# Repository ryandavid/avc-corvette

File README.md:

# log4cxx library symbols missing
```
brew edit log4cxx
```

edit the configure step to look like this (add the last two lines):

```
system "./configure", "--disable-debug", "--disable-dependency-tracking",
                          "--prefix=#{prefix}",
                          # Docs won't install on macOS
                          "--disable-doxygen",
                          "--with-apr=/usr/local/Cellar/apr/1.5.2_3/bin/",
                          "--with-apr-util=/usr/local/Cellar/apr-util/1.5.4_4/bin/"
```

brew reinstall --build-from-source log4cxx

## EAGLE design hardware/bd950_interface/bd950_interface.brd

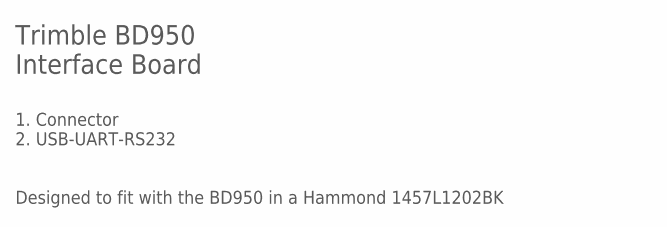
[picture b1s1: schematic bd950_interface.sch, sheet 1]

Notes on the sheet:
Trimble BD950 Interface Board
1. Connector 2. USB-UART-RS232
Designed to fit with the BD950 in a Hammond 1457L1202BK

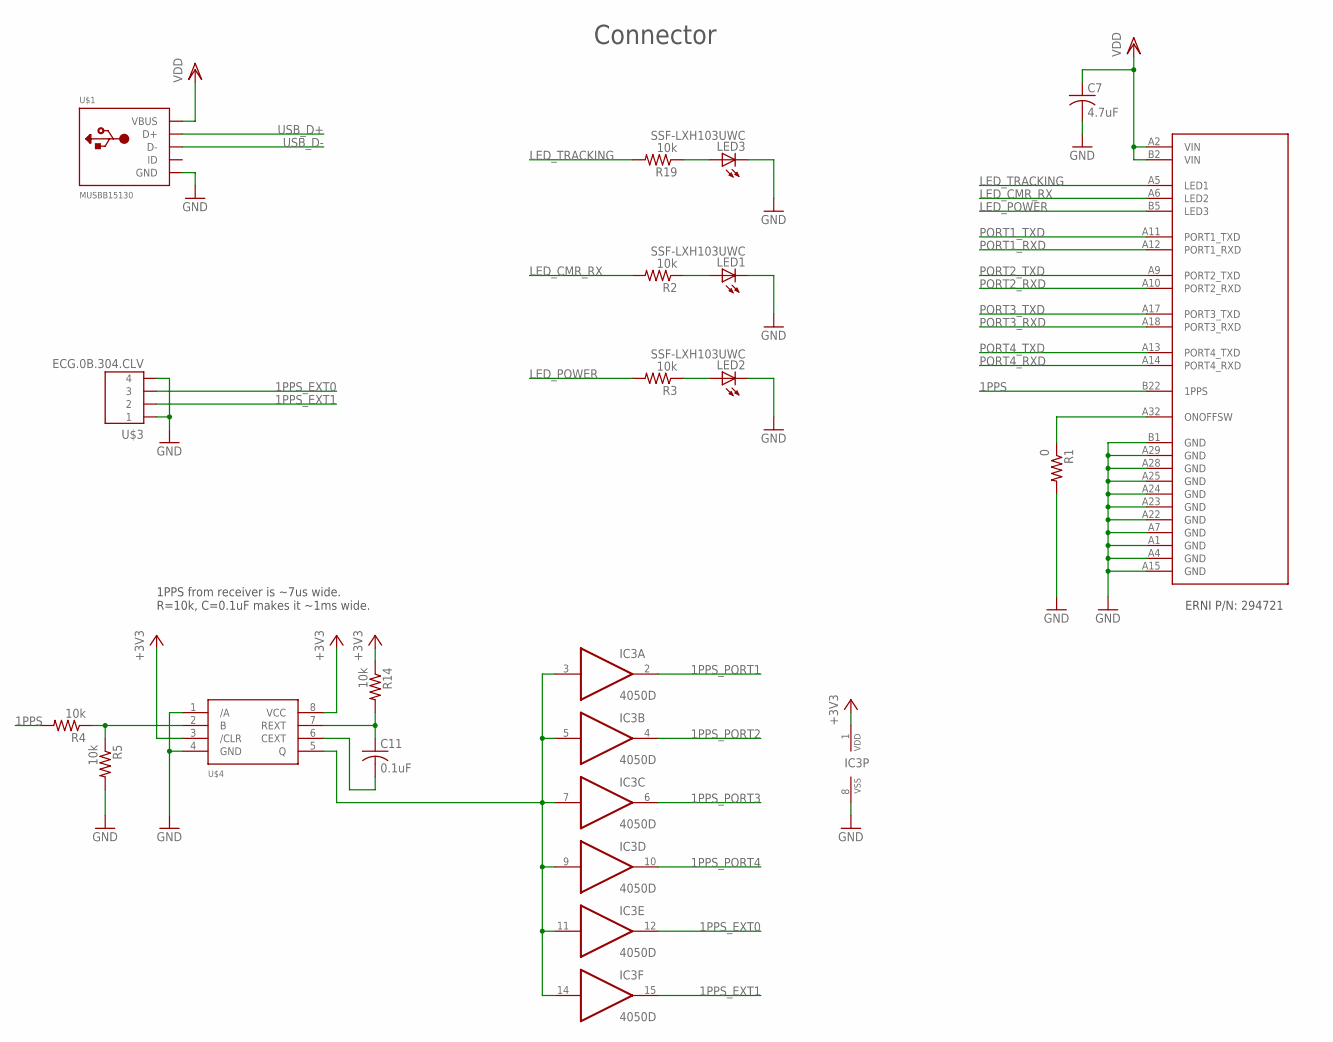
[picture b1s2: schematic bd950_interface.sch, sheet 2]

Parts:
C7: 4.7uF; C0805
C11: 0.1uF; C0603
IC3: 4050D; SO16
LED1, LED2, LED3: SSF-LXH103UWC; CHIP-LED0603
R1: 0; R0603
R2, R3, R4, R5, R14, R19: 10k; R0603
U$1: MUSBB15130
U$2: 294721; TRIMBLE_BD950
U$3: ECG.0B.304.CLV; ECG.0B.CLV
U$4: SN74LVC1G123; DCU_(R-PDSO-G8)

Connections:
1PPS: R4.2, U$2.B22 (1PPS)
1PPS_EXT0: IC3.12 (O), U$3.P$4 (3)
1PPS_EXT1: IC3.15 (O), U$3.P$3 (2)
1PPS_PORT1: IC3.2 (O); also elsewhere on the board
1PPS_PORT2: IC3.4 (O); also elsewhere on the board
1PPS_PORT3: IC3.6 (O); also elsewhere on the board
1PPS_PORT4: IC3.10 (O); also elsewhere on the board
+3V3: IC3.1 (VDD), R14.1, U$4.3 (/CLR), U$4.8 (VCC); also elsewhere on the board
GND: C7.2, IC3.8 (VSS), LED1.C, LED2.C, LED3.C, R1.2, R5.2, U$1.5 (GND), U$2.A1 (GND), U$2.A4 (GND), U$2.A7 (GND), U$2.A15 (GND), U$2.A22 (GND), U$2.A23 (GND), U$2.A24 (GND), U$2.A25 (GND), U$2.A28 (GND), U$2.A29 (GND), U$2.B1 (GND), U$3.P$1 (4), U$3.P$2 (1), U$4.1 (/A), U$4.4 (GND); also elsewhere on the board
LED_CMR_RX: R2.2, U$2.A6 (LED2)
LED_POWER: R3.2, U$2.B5 (LED3)
LED_TRACKING: R19.2, U$2.A5 (LED1)
unnamed: LED1.A, R2.1
unnamed: R1.1, U$2.A32 (ONOFFSW)
unnamed: LED2.A, R3.1
unnamed: LED3.A, R19.1
unnamed: IC3.3 (I), IC3.5 (I), IC3.7 (I), IC3.9 (I), IC3.11 (I), IC3.14 (I), U$4.5 (Q)
unnamed: R4.1, R5.1, U$4.2 (B)
unnamed: C11.2, U$4.6 (CEXT)
unnamed: C11.1, R14.2, U$4.7 (REXT)
PORT1_RXD: U$2.A12 (PORT1_RXD); also elsewhere on the board
PORT1_TXD: U$2.A11 (PORT1_TXD); also elsewhere on the board
PORT2_RXD: U$2.A10 (PORT2_RXD); also elsewhere on the board
PORT2_TXD: U$2.A9 (PORT2_TXD); also elsewhere on the board
PORT3_RXD: U$2.A18 (PORT3_RXD); also elsewhere on the board
PORT3_TXD: U$2.A17 (PORT3_TXD); also elsewhere on the board
PORT4_RXD: U$2.A14 (PORT4_RXD); also elsewhere on the board
PORT4_TXD: U$2.A13 (PORT4_TXD); also elsewhere on the board
USB_D+: U$1.3 (D+); also elsewhere on the board
USB_D-: U$1.2 (D-); also elsewhere on the board
VDD: C7.1, U$1.1 (VBUS), U$2.A2 (VIN), U$2.B2 (VIN); also elsewhere on the board

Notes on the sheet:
Connector
ERNI P/N: 294721
1PPS from receiver is ~7us wide. R=10k, C=0.1uF makes it ~1ms wide.

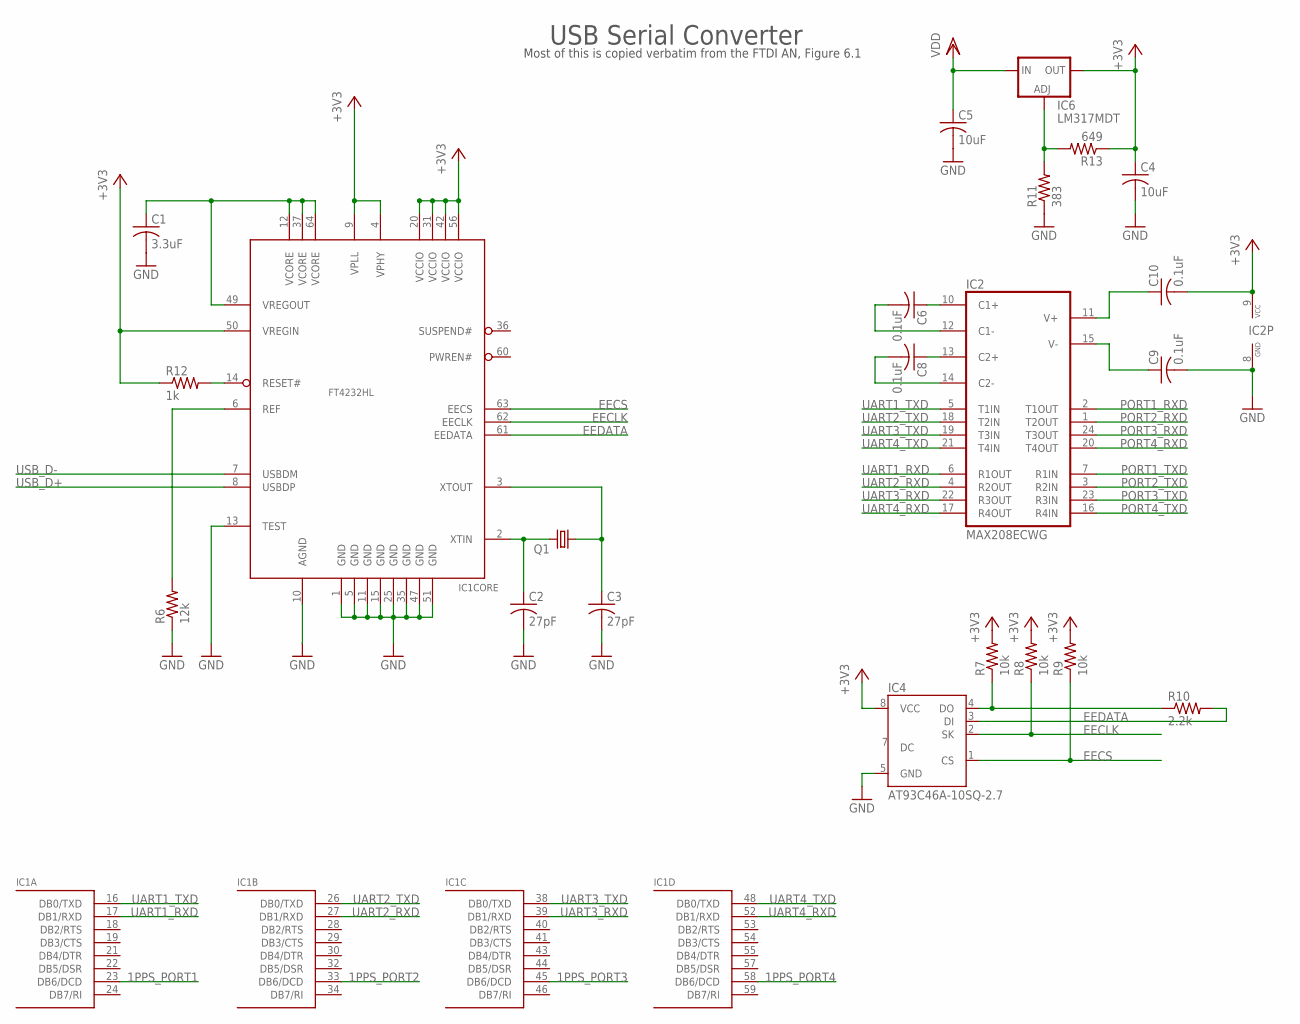
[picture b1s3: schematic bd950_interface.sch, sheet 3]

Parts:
C1: 3.3uF; C0603
C2, C3: 27pF; C0603
C4, C5: 10uF; C0805
C6, C8, C9, C10: 0.1uF; C0603
IC1: FT4232HL; LQFP64
IC2: MAX208ECWG; SO24L
IC4: AT93C46A-10SQ-2.7; SOIC8
IC6: LM317MDT; DPACK
Q1: CRYSTALHC49S; HC49/S
R6: 12k; R0603
R7, R8, R9: 10k; R0603
R10: 2.2k; R0603
R11: 383; R0603
R12: 1k; R0603
R13: 649; R0603

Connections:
1PPS_PORT1: IC1.23 (DB6/DCD); also elsewhere on the board
1PPS_PORT2: IC1.33 (DB6/DCD); also elsewhere on the board
1PPS_PORT3: IC1.45 (DB6/DCD); also elsewhere on the board
1PPS_PORT4: IC1.58 (DB6/DCD); also elsewhere on the board
+3V3: C4.1, C10.2, IC1.4 (VPHY), IC1.9 (VPLL), IC1.20 (VCCIO), IC1.31 (VCCIO), IC1.42 (VCCIO), IC1.50 (VREGIN), IC1.56 (VCCIO), IC2.9 (VCC), IC4.8 (VCC), IC6.4 (OUT), R7.2, R8.2, R9.2, R12.1, R13.1; also elsewhere on the board
EECLK: IC1.62 (EECLK), IC4.2 (SK), R8.1
EECS: IC1.63 (EECS), IC4.1 (CS), R9.1
EEDATA: IC1.61 (EEDATA), IC4.3 (DI), R10.2
GND: C1.2, C2.2, C3.2, C4.2, C5.2, C9.2, IC1.1 (GND), IC1.5 (GND), IC1.10 (AGND), IC1.11 (GND), IC1.13 (TEST), IC1.15 (GND), IC1.25 (GND), IC1.35 (GND), IC1.47 (GND), IC1.51 (GND), IC2.8 (GND), IC4.5 (GND), R6.1, R11.1; also elsewhere on the board
unnamed: IC6.1 (ADJ), R11.2, R13.2
unnamed: IC1.6 (REF), R6.2
unnamed: IC4.4 (DO), R7.1, R10.1
unnamed: C1.1, IC1.12 (VCORE), IC1.37 (VCORE), IC1.49 (VREGOUT), IC1.64 (VCORE)
unnamed: C3.1, IC1.3 (XTOUT), Q1.1
unnamed: C2.1, IC1.2 (XTIN), Q1.2
unnamed: C6.1, IC2.10 (C1+)
unnamed: IC1.14 (RESET#), R12.2
unnamed: C6.2, IC2.12 (C1-)
unnamed: C8.1, IC2.13 (C2+)
unnamed: C8.2, IC2.14 (C2-)
unnamed: C9.1, IC2.15 (V-)
unnamed: C10.1, IC2.11 (V+)
PORT1_RXD: IC2.2 (T1OUT); also elsewhere on the board
PORT1_TXD: IC2.7 (R1IN); also elsewhere on the board
PORT2_RXD: IC2.1 (T2OUT); also elsewhere on the board
PORT2_TXD: IC2.3 (R2IN); also elsewhere on the board
PORT3_RXD: IC2.24 (T3OUT); also elsewhere on the board
PORT3_TXD: IC2.23 (R3IN); also elsewhere on the board
PORT4_RXD: IC2.20 (T4OUT); also elsewhere on the board
PORT4_TXD: IC2.16 (R4IN); also elsewhere on the board
UART1_RXD: IC1.17 (DB1/RXD), IC2.6 (R1OUT)
UART1_TXD: IC1.16 (DB0/TXD), IC2.5 (T1IN)
UART2_RXD: IC1.27 (DB1/RXD), IC2.4 (R2OUT)
UART2_TXD: IC1.26 (DB0/TXD), IC2.18 (T2IN)
UART3_RXD: IC1.39 (DB1/RXD), IC2.22 (R3OUT)
UART3_TXD: IC1.38 (DB0/TXD), IC2.19 (T3IN)
UART4_RXD: IC1.52 (DB1/RXD), IC2.17 (R4OUT)
UART4_TXD: IC1.48 (DB0/TXD), IC2.21 (T4IN)
USB_D+: IC1.8 (USBDP); also elsewhere on the board
USB_D-: IC1.7 (USBDM); also elsewhere on the board
VDD: C5.1, IC6.3 (IN); also elsewhere on the board

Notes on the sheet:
USB Serial Converter
Most of this is copied verbatim from the FTDI AN, Figure 6.1

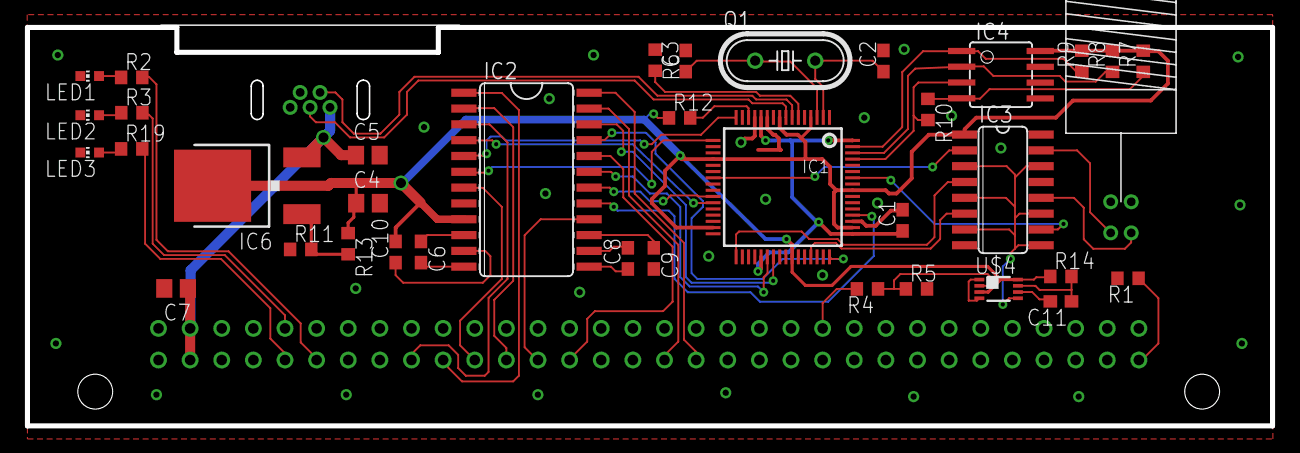
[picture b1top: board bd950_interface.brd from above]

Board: 2 copper layers, 100.0 x 32.0 mm, 39 parts (0 on the bottom side), 55 nets.

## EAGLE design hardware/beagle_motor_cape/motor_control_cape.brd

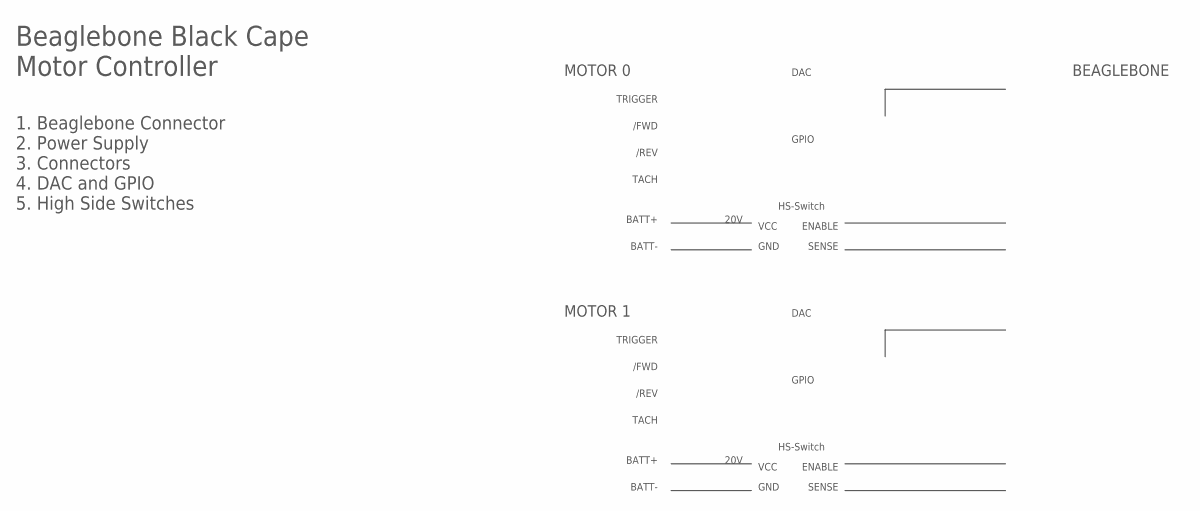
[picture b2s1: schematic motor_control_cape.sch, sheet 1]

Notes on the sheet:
Beaglebone Black Cape Motor Controller
1. Beaglebone Connector 2. Power Supply 3. Connectors 4. DAC and GPIO 5. High Side Switches
MOTOR 0
/FWD
/REV
TACH
BATT+
BATT-
HS-Switch
VCC
GND
ENABLE
SENSE
20V
GPIO
DAC
TRIGGER
MOTOR 1
BEAGLEBONE

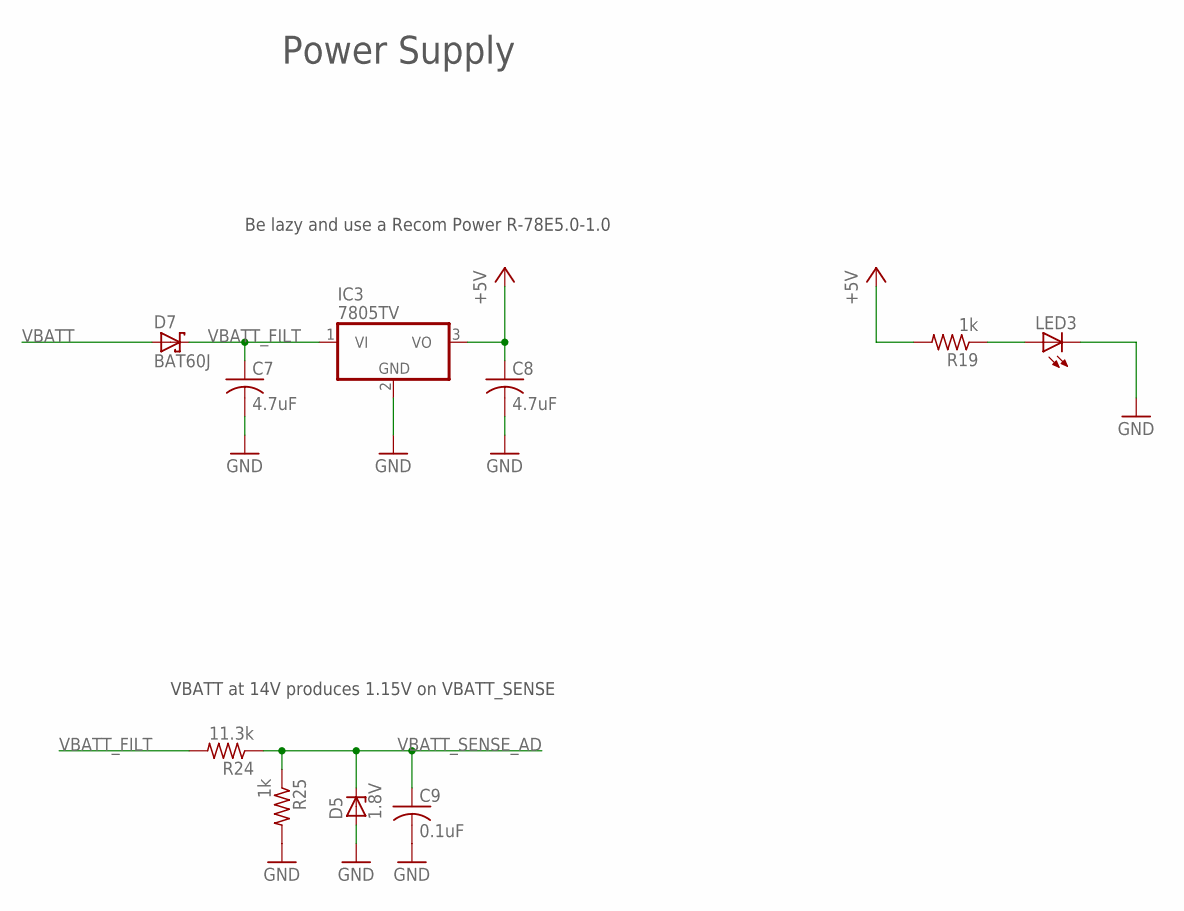
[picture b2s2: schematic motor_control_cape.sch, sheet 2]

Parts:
C7, C8: 4.7uF; C0805
C9: 0.1uF; C0603
D5: 1.8V; SOT23
D7: BAT60J; SOD323_ST
IC3: 7805TV; TO220V
LED3: LEDCHIPLED_0603; CHIPLED_0603
R19, R25: 1k; R0603
R24: 11.3k; R0603

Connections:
+5V: C8.1, IC3.3 (VO), R19.2; also elsewhere on the board
GND: C7.2, C8.2, C9.2, D5.1 (A), IC3.2 (GND), LED3.C, R25.2; also elsewhere on the board
unnamed: LED3.A, R19.1
VBATT: D7.A; also elsewhere on the board
VBATT_FILT: C7.1, D7.C, IC3.1 (VI), R24.2
VBATT_SENSE_AD: C9.1, D5.3 (C), R24.1, R25.1; also elsewhere on the board

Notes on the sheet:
Power Supply
VBATT at 14V produces 1.15V on VBATT_SENSE
Be lazy and use a Recom Power R-78E5.0-1.0

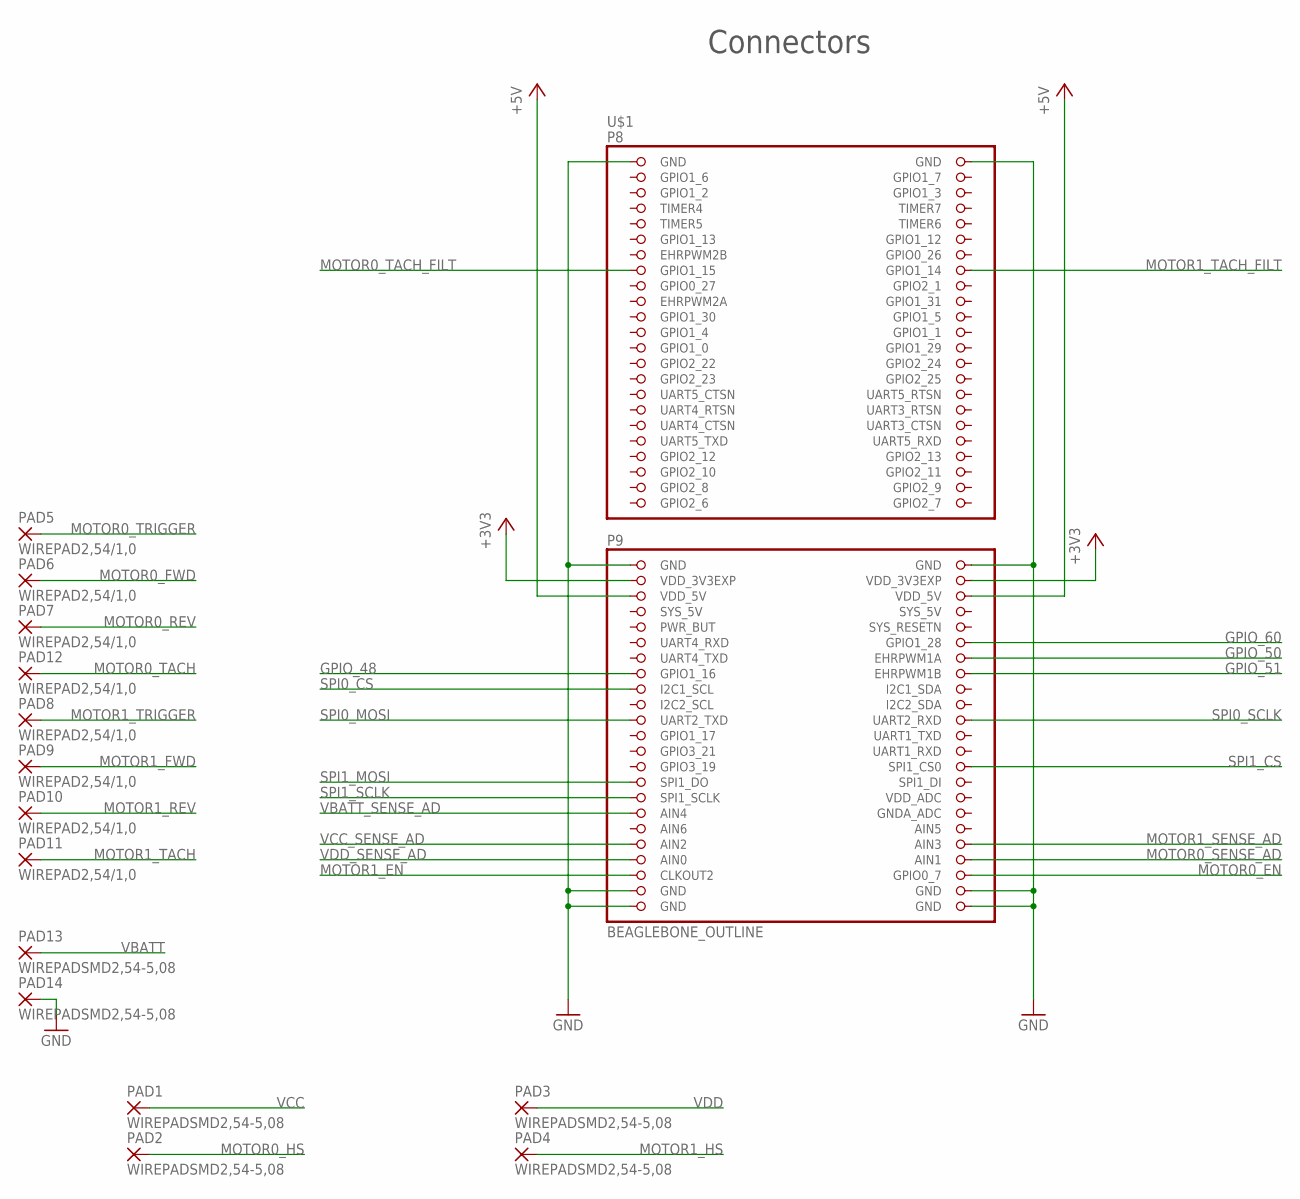
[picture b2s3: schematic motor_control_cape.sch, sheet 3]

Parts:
PAD1, PAD2, PAD3, PAD4, PAD13, PAD14: WIREPADSMD2,54-5,08; SMD2,54-5,08
PAD5, PAD6, PAD7, PAD8, PAD9, PAD10, PAD11, PAD12: WIREPAD2,54/1,0; 2,54/1,0
U$1: BEAGLEBONE_OUTLINE; BEAGLEBONE_SHIELD

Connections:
+3V3: U$1.49 (VDD_3V3EXP), U$1.50 (VDD_3V3EXP); also elsewhere on the board
+5V: U$1.51 (VDD_5V), U$1.52 (VDD_5V); also elsewhere on the board
GND: PAD14.1, U$1.1 (GND), U$1.2 (GND), U$1.47 (GND), U$1.48 (GND), U$1.89 (GND), U$1.90 (GND), U$1.91 (GND), U$1.92 (GND); also elsewhere on the board
GPIO_48: U$1.61 (GPIO1_16); also elsewhere on the board
GPIO_50: U$1.60 (EHRPWM1A); also elsewhere on the board
GPIO_51: U$1.62 (EHRPWM1B); also elsewhere on the board
GPIO_60: U$1.58 (GPIO1_28); also elsewhere on the board
MOTOR0_EN: U$1.88 (GPIO0_7); also elsewhere on the board
MOTOR0_FWD: PAD6.1; also elsewhere on the board
MOTOR0_HS: PAD2.1; also elsewhere on the board
MOTOR0_REV: PAD7.1; also elsewhere on the board
MOTOR0_SENSE_AD: U$1.86 (AIN1); also elsewhere on the board
MOTOR0_TACH: PAD12.1; also elsewhere on the board
MOTOR0_TACH_FILT: U$1.15 (GPIO1_15); also elsewhere on the board
MOTOR0_TRIGGER: PAD5.1; also elsewhere on the board
MOTOR1_EN: U$1.87 (CLKOUT2); also elsewhere on the board
MOTOR1_FWD: PAD9.1; also elsewhere on the board
MOTOR1_HS: PAD4.1; also elsewhere on the board
MOTOR1_REV: PAD10.1; also elsewhere on the board
MOTOR1_SENSE_AD: U$1.84 (AIN3); also elsewhere on the board
MOTOR1_TACH: PAD11.1; also elsewhere on the board
MOTOR1_TACH_FILT: U$1.16 (GPIO1_14); also elsewhere on the board
MOTOR1_TRIGGER: PAD8.1; also elsewhere on the board
SPI0_CS: U$1.63 (I2C1_SCL); also elsewhere on the board
SPI0_MOSI: U$1.67 (UART2_TXD); also elsewhere on the board
SPI0_SCLK: U$1.68 (UART2_RXD); also elsewhere on the board
SPI1_CS: U$1.74 (SPI1_CS0); also elsewhere on the board
SPI1_MOSI: U$1.75 (SPI1_DO); also elsewhere on the board
SPI1_SCLK: U$1.77 (SPI1_SCLK); also elsewhere on the board
SYS_5V: U$1.53 (SYS_5V)
VBATT: PAD13.1; also elsewhere on the board
VBATT_SENSE_AD: U$1.79 (AIN4); also elsewhere on the board
VCC: PAD1.1; also elsewhere on the board
VCC_SENSE_AD: U$1.83 (AIN2); also elsewhere on the board
VDD: PAD3.1; also elsewhere on the board
VDD_SENSE_AD: U$1.85 (AIN0); also elsewhere on the board

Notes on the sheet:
Connectors

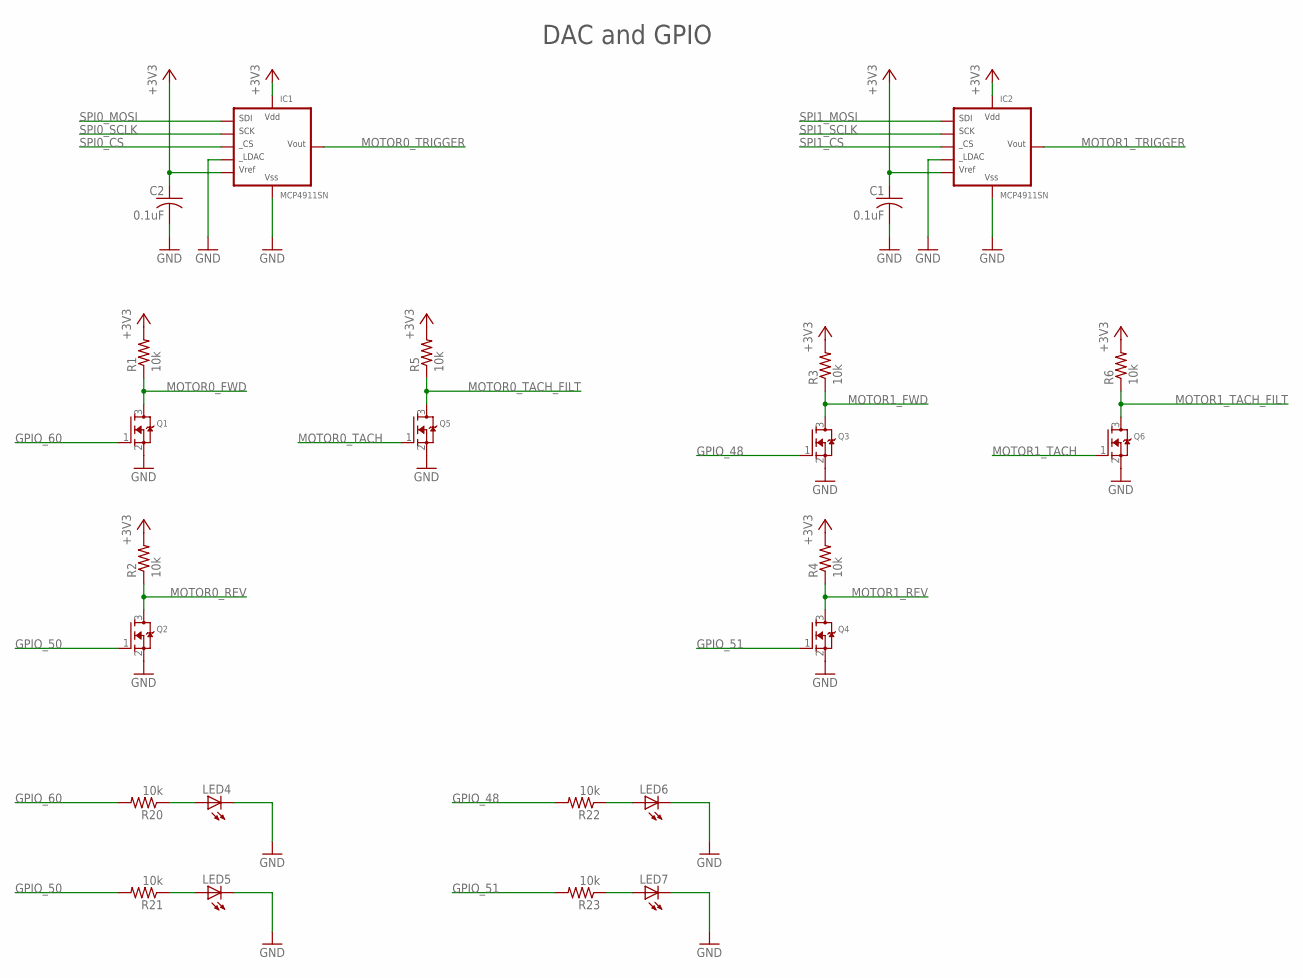
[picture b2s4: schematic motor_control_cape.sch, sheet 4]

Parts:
C1, C2: 0.1uF; C0603
IC1, IC2: MCP4911SN; SO-08
LED4, LED5, LED6, LED7: LEDCHIPLED_0603; CHIPLED_0603
Q1, Q2, Q3, Q4, Q5, Q6: MOSFET-NREFLOW; SOT23
R1, R2, R3, R4, R5, R6, R20, R21, R22, R23: 10k; R0603

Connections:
+3V3: C1.1, C2.1, IC1.1 (VDD), IC1.6 (VREF), IC2.1 (VDD), IC2.6 (VREF), R1.2, R2.2, R3.2, R4.2, R5.2, R6.2; also elsewhere on the board
GND: C1.2, C2.2, IC1.5 (LDAC), IC1.7 (VSS), IC2.5 (LDAC), IC2.7 (VSS), LED4.C, LED5.C, LED6.C, LED7.C, Q1.2 (S), Q2.2 (S), Q3.2 (S), Q4.2 (S), Q5.2 (S), Q6.2 (S); also elsewhere on the board
GPIO_48: Q3.1 (G), R22.2; also elsewhere on the board
GPIO_50: Q2.1 (G), R21.2; also elsewhere on the board
GPIO_51: Q4.1 (G), R23.2; also elsewhere on the board
GPIO_60: Q1.1 (G), R20.2; also elsewhere on the board
MOTOR0_FWD: Q1.3 (D), R1.1; also elsewhere on the board
MOTOR0_REV: Q2.3 (D), R2.1; also elsewhere on the board
MOTOR0_TACH: Q5.1 (G); also elsewhere on the board
MOTOR0_TACH_FILT: Q5.3 (D), R5.1; also elsewhere on the board
MOTOR0_TRIGGER: IC1.8 (VOUT); also elsewhere on the board
MOTOR1_FWD: Q3.3 (D), R3.1; also elsewhere on the board
MOTOR1_REV: Q4.3 (D), R4.1; also elsewhere on the board
MOTOR1_TACH: Q6.1 (G); also elsewhere on the board
MOTOR1_TACH_FILT: Q6.3 (D), R6.1; also elsewhere on the board
MOTOR1_TRIGGER: IC2.8 (VOUT); also elsewhere on the board
unnamed: LED4.A, R20.1
unnamed: LED5.A, R21.1
unnamed: LED6.A, R22.1
unnamed: LED7.A, R23.1
SPI0_CS: IC1.2 (CS); also elsewhere on the board
SPI0_MOSI: IC1.4 (SDI); also elsewhere on the board
SPI0_SCLK: IC1.3 (SCK); also elsewhere on the board
SPI1_CS: IC2.2 (CS); also elsewhere on the board
SPI1_MOSI: IC2.4 (SDI); also elsewhere on the board
SPI1_SCLK: IC2.3 (SCK); also elsewhere on the board

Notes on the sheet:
DAC and GPIO

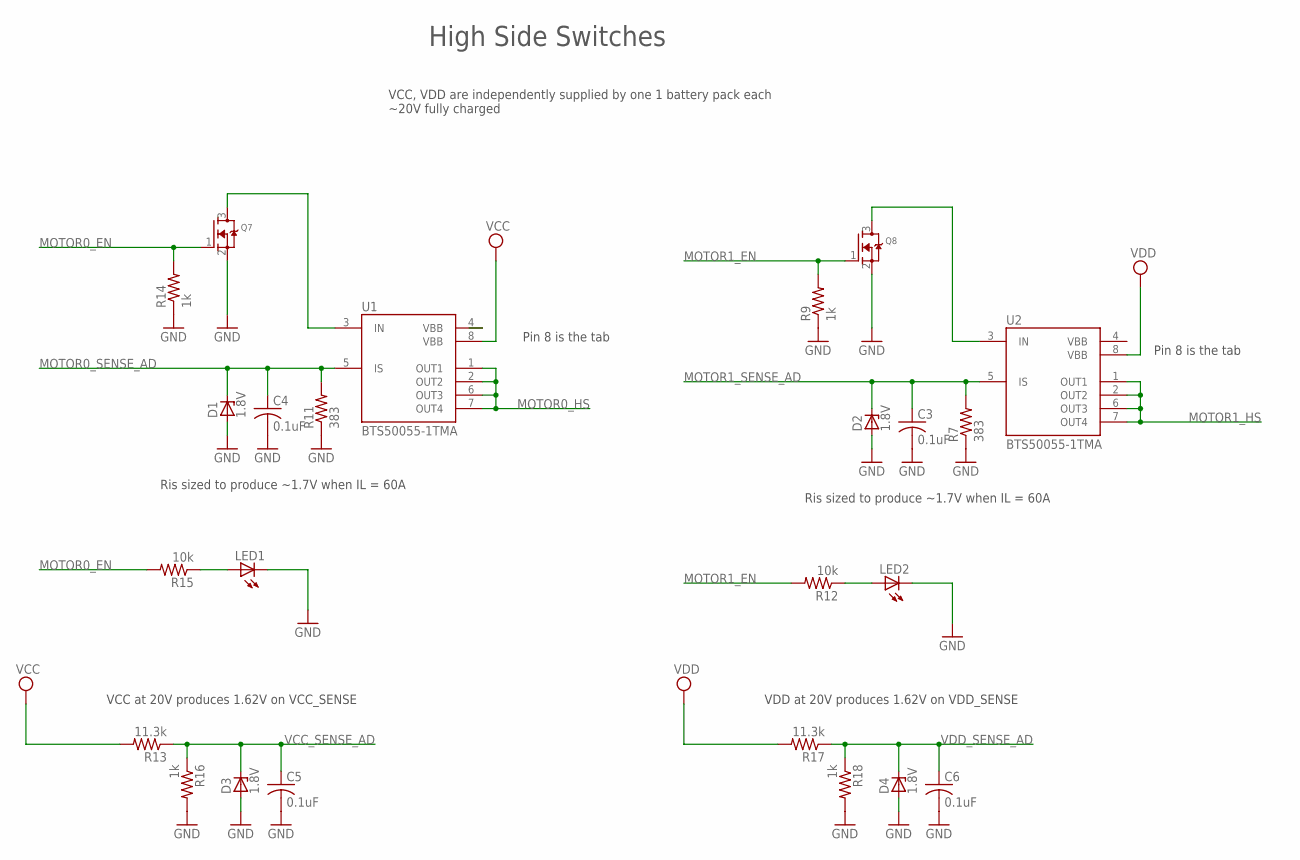
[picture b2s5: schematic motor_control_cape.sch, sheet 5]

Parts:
C3, C4, C5, C6: 0.1uF; C0603
D1, D2, D3, D4: 1.8V; SOT23
LED1, LED2: LEDCHIPLED_0603; CHIPLED_0603
Q7, Q8: MOSFET-NREFLOW; SOT23
R7, R11: 383; R0603
R9, R14, R16, R18: 1k; R0603
R12, R15: 10k; R0603
R13, R17: 11.3k; R0603
U1, U2: BTS50055-1TMA; TO127P1385X450-8N-V

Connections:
GND: C3.2, C4.2, C5.2, C6.2, D1.1 (A), D2.1 (A), D3.1 (A), D4.1 (A), LED1.C, LED2.C, Q7.2 (S), Q8.2 (S), R7.1, R9.1, R11.1, R14.1, R16.2, R18.2; also elsewhere on the board
MOTOR0_EN: Q7.1 (G), R14.2, R15.2; also elsewhere on the board
MOTOR0_HS: U1.1 (OUT1), U1.2 (OUT2), U1.6 (OUT3), U1.7 (OUT4); also elsewhere on the board
MOTOR0_SENSE_AD: C4.1, D1.3 (C), R11.2, U1.5 (IS); also elsewhere on the board
MOTOR1_EN: Q8.1 (G), R9.2, R12.2; also elsewhere on the board
MOTOR1_HS: U2.1 (OUT1), U2.2 (OUT2), U2.6 (OUT3), U2.7 (OUT4); also elsewhere on the board
MOTOR1_SENSE_AD: C3.1, D2.3 (C), R7.2, U2.5 (IS); also elsewhere on the board
unnamed: Q8.3 (D), U2.3 (IN)
unnamed: LED2.A, R12.1
unnamed: Q7.3 (D), U1.3 (IN)
unnamed: LED1.A, R15.1
VBB: U2.4 (VBB)
VCC: R13.2, U1.8 (VBB); also elsewhere on the board
VCC_SENSE_AD: C5.1, D3.3 (C), R13.1, R16.1; also elsewhere on the board
VDD: R17.2, U2.8 (VBB); also elsewhere on the board
VDD_SENSE_AD: C6.1, D4.3 (C), R17.1, R18.1; also elsewhere on the board

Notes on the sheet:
High Side Switches
Ris sized to produce ~1.7V when IL = 60A
VCC, VDD are independently supplied by one 1 battery pack each ~20V fully charged
VCC at 20V produces 1.62V on VCC_SENSE
VDD at 20V produces 1.62V on VDD_SENSE
Pin 8 is the tab

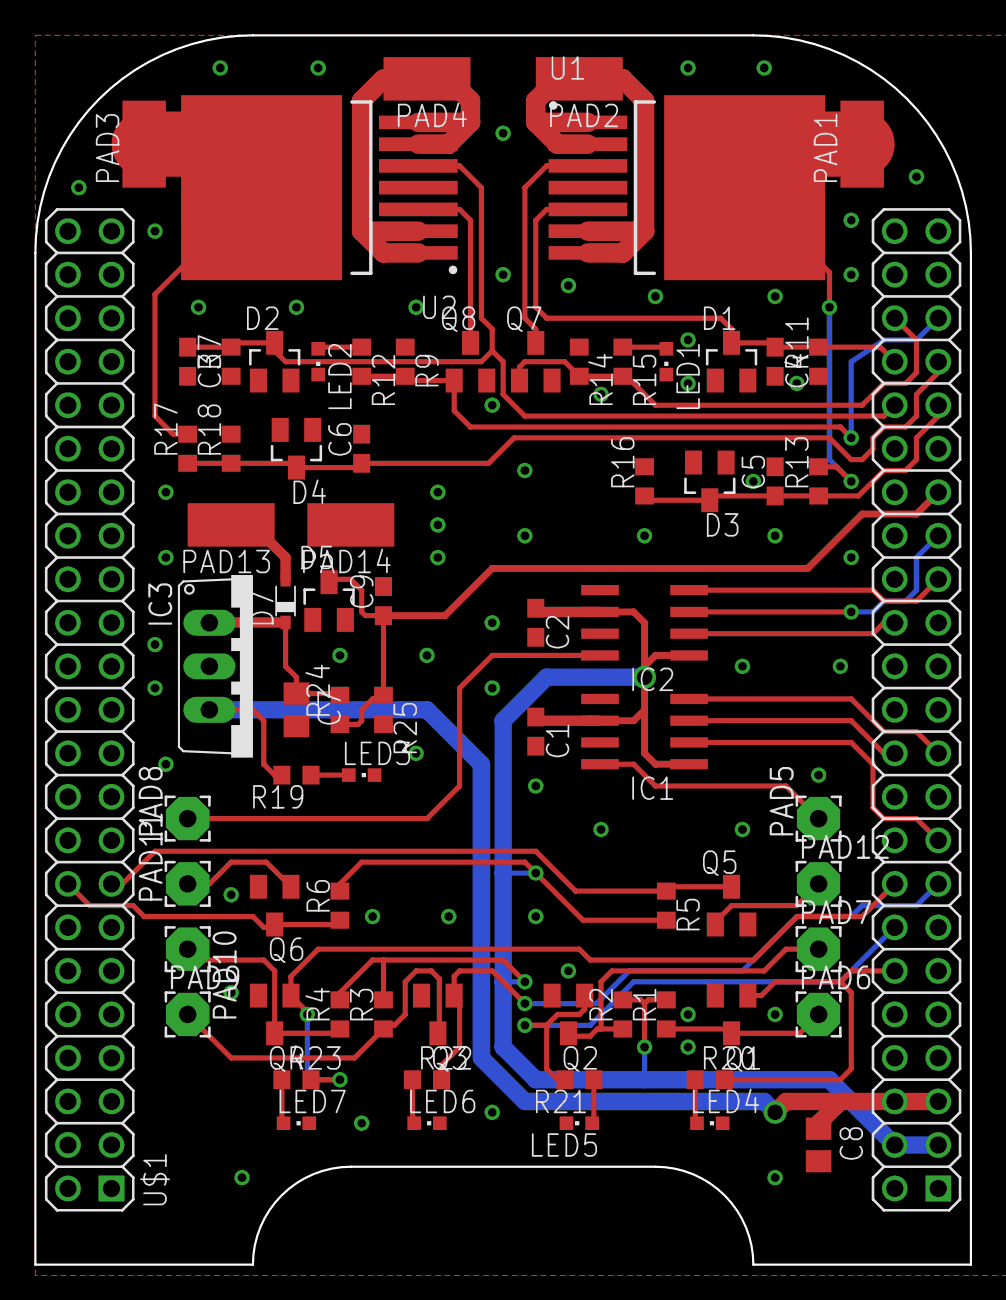
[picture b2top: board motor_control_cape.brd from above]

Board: 2 copper layers, 54.6 x 71.8 mm, 73 parts (0 on the bottom side), 45 nets.

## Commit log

2016-11-01 Clean up workspace and start on BD950 driver
2016-11-14 Working Trimble BD950 driver
2016-11-14 Touch up CMakelists
2016-11-15 Add modified macOS install scripts
2016-11-17 Add instructions for fixing log4cxx on macOS
2016-11-20 Switch to ROS Desktop on macOS
2016-11-22 Clean up BD950 driver
2016-11-22 Fix build using catkin build
2016-11-23 Add robot_localization package
2016-11-25 Add timeout and reconnect to NTRIP client
2016-11-26 Add RTCMv2 parser
2016-11-27 Hackily convert RTCM parser into ROS node
2016-11-29 WIP Add latency measurements for NTRIP
2016-12-15 Inital POC for motor controller via SPI DAC
2016-12-18 Add Joystick interface for macOS
2016-12-18 Publish NTRIP observation latency
2016-12-19 Real motor control working with direction
2016-12-24 Bringup notes for Beaglebone Black motor controller
2016-12-24 Fix build issues
2017-01-01 Move motor control GPIO and SPI into their own lib
2017-01-02 Add executables to install path, and add script to create debian.
2017-01-02 Fix missing path on Debian build script
2017-01-02 No, seriously, actually fix the Debian path
2017-01-07 Update Beaglebone Black bringup
2017-01-07 Add stdlib to motor_control
2017-01-07 Add additional packages required for Beaglebone Black bringup
2017-01-09 Remove local build script and add Jenkins build script
2017-01-11 Add bringup instructions for Ubuntu server, and fix build
2017-01-11 More tweaks to Jenkins build, switch to monotonic build versioning
2017-01-14 Fix motor control calcs
2017-01-16 Start beaglebone motor cape
2017-01-18 Add macOS packaging to Jenkins build script
2017-01-23 Add BeagleBone PRU assembler and loader
2017-01-23 Add PRU Example
2017-01-23 Fix build on macOS
2017-01-23 Really fix build this time
2017-01-31 Continue work on BeagleBone Black cape
2017-02-03 Working PRU GPIO example in C
2017-02-05 Update Documentation and tweak CMakeLists for pru_example
2017-02-05 Fix pru_example CMakeList on armhf
2017-02-05 Generate C headers from PRU binaries to be used with prussdrv_exec_code
2017-02-05 Add additional pins to BB PRU DTC
2017-02-05 Move PRU_ICSS Headers to pru_utils
2017-02-05 Fix PRU include move
2017-02-06 Add cmake macro and find_package for TI PRU stuff
2017-02-07 Pull in PRU example into motor_control node
2017-02-13 Finish motor control cape schematic
2017-02-15 More layout on motor control cape
2017-02-16 Finish laying out motor control cape
2017-02-18 Fix BD950 subscription to NTRIP corrections
2017-02-18 Start interface board for BD950
2017-02-18 Change BD950 measurement rate from 20Hz to 10Hz to avoid sawtooth in longitude
2017-02-20 Add KML server to display rover position in realtime
2017-02-21 Continue work on BD950 interface board
2017-02-22 Make BD950 interface board USB powered
2017-03-01 Continue laying out BD950 interface board
2017-03-02 Finish laying out BD950 interface board
2017-03-06 Start of system utilization reporting
2017-03-06 Fix system reportion on Linux
2017-03-08 Add docker containers for x86 and armhf targets
2017-03-09 Touch up Ubuntu 16.04 x86 Dockerfile
2017-03-11 Add basic startup script and update Ubuntu bringup doc
2017-03-11 Add NVML library for system stats reporting
2017-03-26 Enable PORT2 and 1PPS on BD950
2017-04-03 WIP Fix BD950 interface board layout issues
2017-04-09 Rev 2 of BD950 interface board
2017-04-09 Add ZDA messages to Port 2 on BD950
